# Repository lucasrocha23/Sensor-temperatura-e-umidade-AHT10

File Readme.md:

<p align='center'> Sensor de Temperatura e Umidade AHT10 </p>

Projeto de Sistemas Embarcados

Grupo

Lucas Rocha do Ó Lira Lins <br>
Ramon Lino de Souza Pereira <br>
Igor Henrique Martins Araujo

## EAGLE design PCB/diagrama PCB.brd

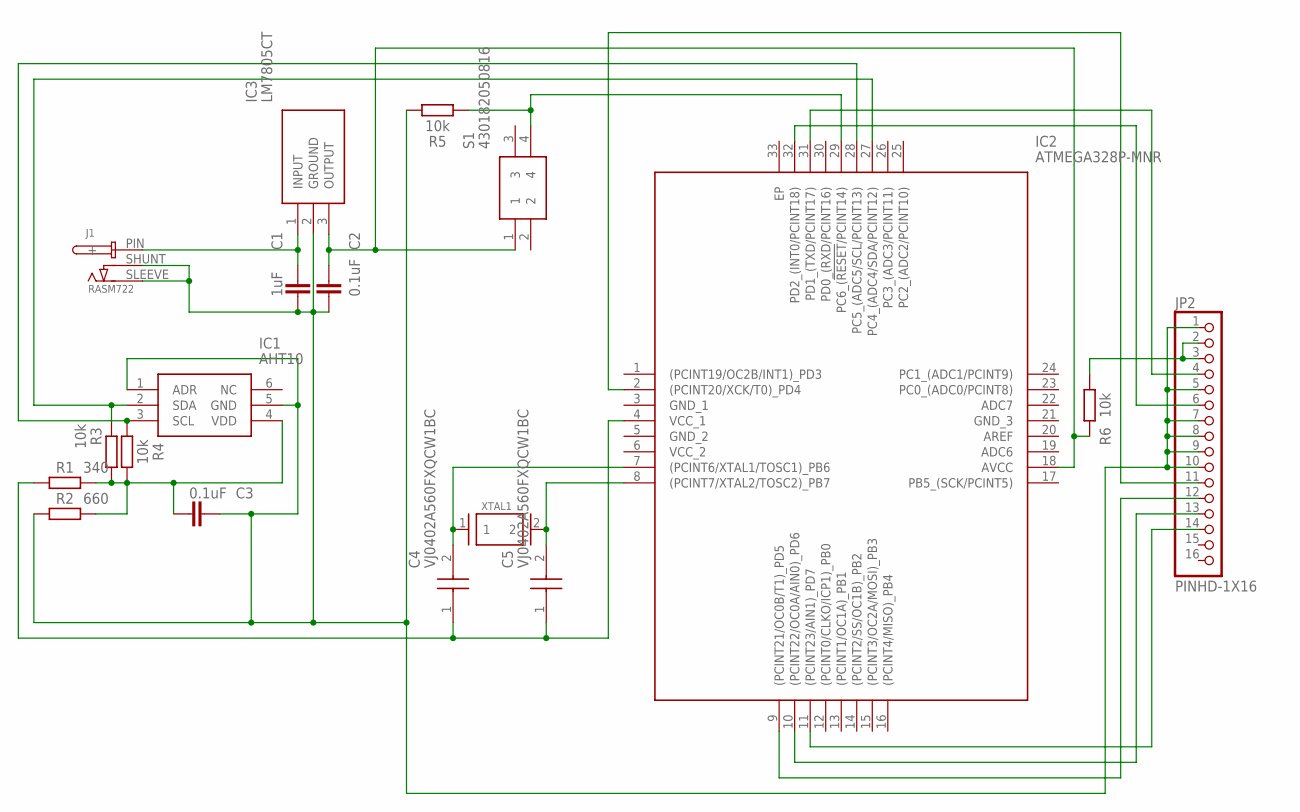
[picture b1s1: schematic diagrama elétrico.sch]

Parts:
C1: 1uF; CAPC1005X60
C2, C3: 0.1uF; CAPC1005X60
C4, C5: VJ0402A560FXQCW1BC; CAPC1005X55N
IC1: AHT10
IC2: ATMEGA328P-MNR; QFN50P500X500X100-33N
IC3: LM7805CT; TO254P470X1028X1955-3P
J1: RASM722; RASM722X
JP2: PINHD-1X16; 1X16
R1: 340; RESC6332X71
R2: 660; RESC6332X71
R3, R4, R5, R6: 10k; RESC6332X71
S1: 430182050816; 430182070816
XTAL1: 16MHz; XTAL1170X500X450N

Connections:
GND: C1.2, C2.2, C3.1, IC1.1 (ADR), IC1.5 (GND), IC3.2 (GROUND), J1.SHUNT (-), J1.SLEEVE (NEG), JP2.1, JP2.5, JP2.7, JP2.8, JP2.9, JP2.10, R2.1, R5.1
unnamed: IC1.3 (SCL), IC2.28 (PC5_(ADC5/SCL/PCINT13)), R4.2
unnamed: C4.2, IC2.7 ((PCINT6/XTAL1/TOSC1)_PB6), XTAL1.1
unnamed: C3.2, IC1.4 (VDD), R1.2, R2.2, R3.1, R4.1
unnamed: C5.2, IC2.8 ((PCINT7/XTAL2/TOSC2)_PB7), XTAL1.2
unnamed: C1.1, IC3.1 (INPUT), J1.PIN (+)
unnamed: JP2.2, JP2.3, R6.2
unnamed: IC1.2 (SDA), IC2.27 (PC4_(ADC4/SDA/PCINT12)), R3.2
unnamed: C2.1, IC2.18 (AVCC), IC3.3 (OUTPUT), R6.1, S1.1
unnamed: IC2.29 (PC6_(!RESET!/PCINT14)), R5.2, S1.4
unnamed: C4.1, C5.1, IC2.4 (VCC_1), R1.1
unnamed: IC2.31 (PD1_(TXD/PCINT17)), JP2.4
unnamed: IC2.32 (PD2_(INT0/PCINT18)), JP2.6
unnamed: IC2.11 ((PCINT23/AIN1)_PD7), JP2.14
unnamed: IC2.10 ((PCINT22/OC0A/AIN0)_PD6), JP2.13
unnamed: IC2.9 ((PCINT21/OC0B/T1)_PD5), JP2.12
unnamed: IC2.2 ((PCINT20/XCK/T0)_PD4), JP2.11

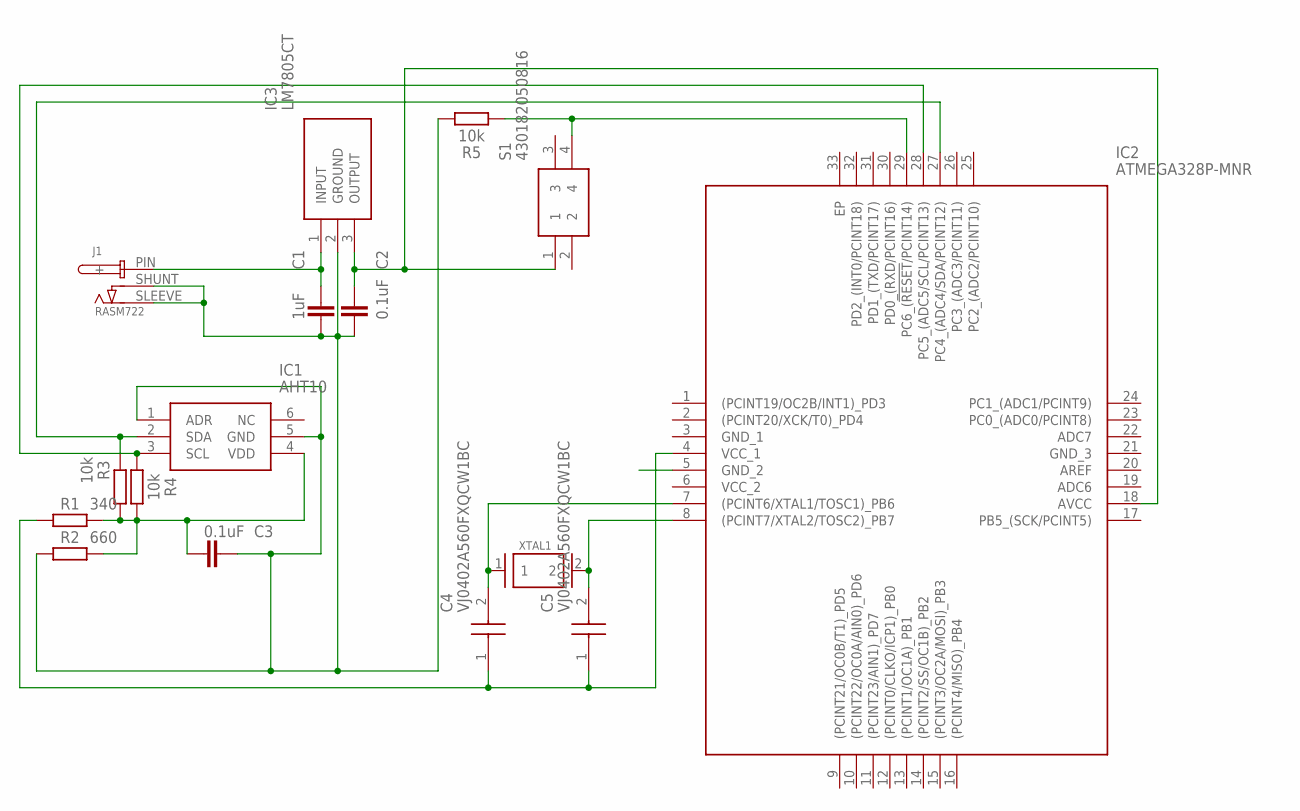
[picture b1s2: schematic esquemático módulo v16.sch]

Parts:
C1: 1uF; CAPC1005X60
C2, C3: 0.1uF; CAPC1005X60
C4, C5: VJ0402A560FXQCW1BC; CAPC1005X55N
IC1: AHT10
IC2: ATMEGA328P-MNR; QFN50P500X500X100-33N
IC3: LM7805CT; TO254P470X1028X1955-3P
J1: RASM722; RASM722X
R1: 340; RESC6332X71
R2: 660; RESC6332X71
R3, R4, R5: 10k; RESC6332X71
S1: 430182050816; 430182070816
XTAL1: 16MHz; XTAL1170X500X450N

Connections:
GND: C1.2, C2.2, C3.1, IC1.1 (ADR), IC1.5 (GND), IC3.2 (GROUND), J1.SHUNT (-), J1.SLEEVE (NEG), R2.1, R5.1; also elsewhere on the board
unnamed: IC1.3 (SCL), IC2.28 (PC5_(ADC5/SCL/PCINT13)), R4.2
unnamed: C4.2, IC2.7 ((PCINT6/XTAL1/TOSC1)_PB6), XTAL1.1
unnamed: C3.2, IC1.4 (VDD), R1.2, R2.2, R3.1, R4.1
unnamed: C5.2, IC2.8 ((PCINT7/XTAL2/TOSC2)_PB7), XTAL1.2
unnamed: C1.1, IC3.1 (INPUT), J1.PIN (+)
unnamed: IC1.2 (SDA), IC2.27 (PC4_(ADC4/SDA/PCINT12)), R3.2
unnamed 8: C2.1, IC2.18 (AVCC), IC3.3 (OUTPUT), S1.1; also elsewhere on the board
unnamed: IC2.29 (PC6_(!RESET!/PCINT14)), R5.2, S1.4
unnamed: C4.1, C5.1, IC2.4 (VCC_1), R1.1

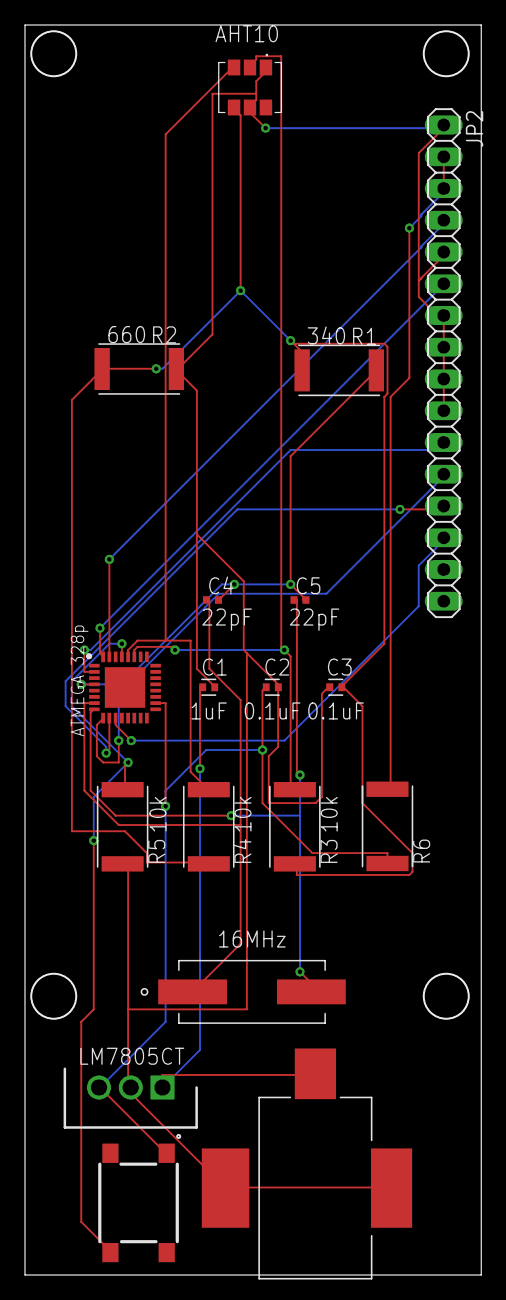
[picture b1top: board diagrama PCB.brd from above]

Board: 2 copper layers, 36.3 x 99.8 mm, 18 parts (0 on the bottom side), 17 nets.

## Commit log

2021-10-19 Rename Readme.txt to Readme.md
2021-10-19 vídeo fatiador
2021-10-19 adição do fluxograma
